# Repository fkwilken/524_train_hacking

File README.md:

# Lionel Train Hacking Project

## ESP32 / NRF24 Transmitter

The ESP32 code is built using [platformio](https://platformio.org/). 
Get the VS Code extension or install it and use:
- `pio run` to build
- `pio run -t upload` to upload

The NRF transmitter chip is driven using the [RF24](https://nrf24.github.io/RF24/) arduino library.

- To change the frequency, use `radio.setChannel(offset);`, where offset is the integer frequency offset from 2400 Mhz.
- To jam the pairing, use `radio.setChannel(40);` to broadcast at the pairing frequency of 2440 Mhz.
- To jam the train while it is running, use an SDR to find the approximate frequency that the train is running on
  - Use one transmitter board to jam the pairing frequency, 2440 Mhz
  - Reprogram a second transmitter board to jam the actively running frequency. For example, if you see activity at 2420 Mhz, set the channel to 20.

## PCB

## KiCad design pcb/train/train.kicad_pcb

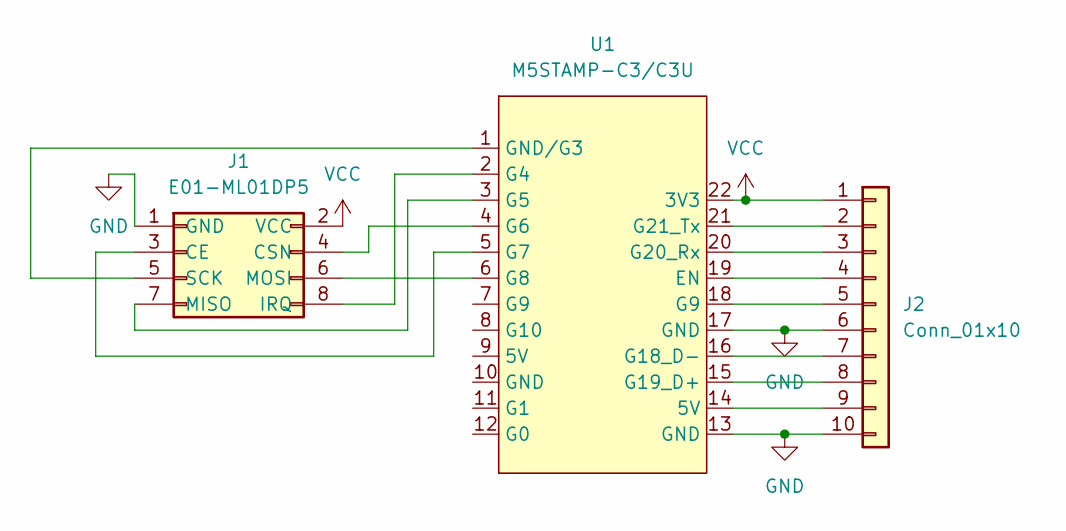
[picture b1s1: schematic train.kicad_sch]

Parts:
J1: E01-ML01DP5
J2: Conn_01x10; PinHeader_1x10_P2.54mm_Vertical
U1: M5STAMP-C3/C3U; M5STAMP-C3C3U

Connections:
GND: J1.1 (GND), J2.6, J2.10, U1.13 (GND), U1.17 (GND)
unnamed: J1.3 (CE), U1.5 (G7)
unnamed: J1.4 (CSN), U1.4 (G6)
unnamed: J1.8 (IRQ), U1.2 (G4)
unnamed: J1.7 (MISO), U1.3 (G5)
unnamed: J1.6 (MOSI), U1.6 (G8)
unnamed: J1.5 (SCK), U1.1 (GND/G3)
unnamed: J2.2, U1.21 (G21_Tx)
unnamed: J2.3, U1.20 (G20_Rx)
unnamed: J2.4, U1.19 (EN)
unnamed: J2.5, U1.18 (G9)
unnamed: J2.7, U1.16 (G18_D-)
unnamed: J2.8, U1.15 (G19_D+)
unnamed: J2.9, U1.14 (5V)
VCC: J1.2 (VCC), J2.1, U1.22 (3V3)

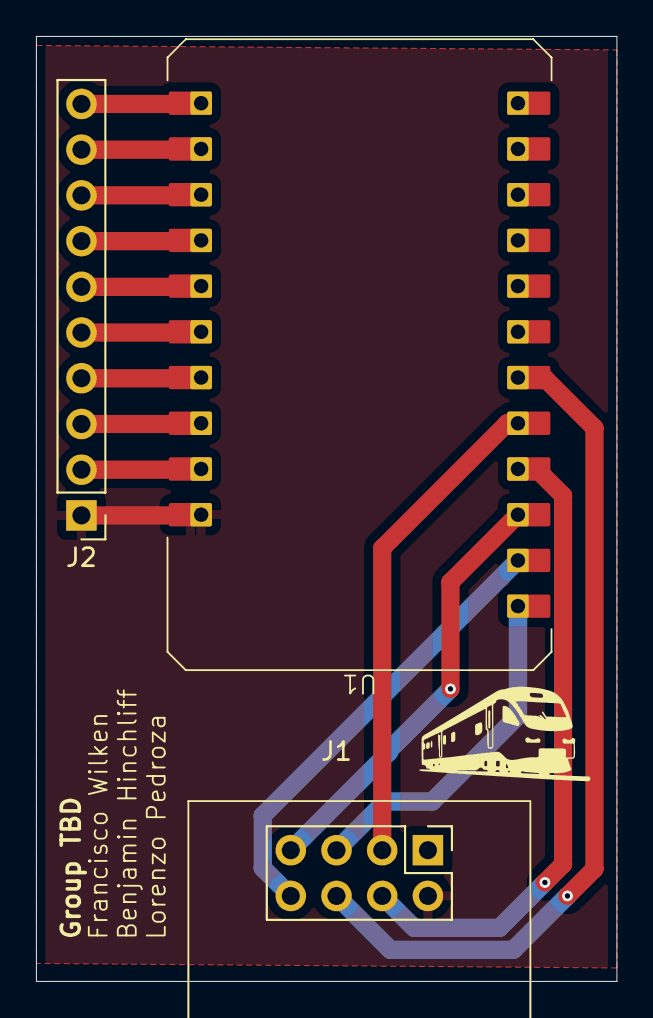
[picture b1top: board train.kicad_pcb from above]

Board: 2 copper layers, 32.2 x 52.5 mm, 3 parts (0 on the bottom side), 15 nets.

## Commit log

2025-03-06 Initial Setup
2025-03-06 Add PCB
2025-03-06 Tx and RX Test
2025-03-08 Remove delay from loop
2025-03-10 commented out lines to do a transmit demo
2025-03-11 Jamming Attack
